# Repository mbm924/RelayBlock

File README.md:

# RelayBlock
A relay block pcb with current sensing for raspberry pi

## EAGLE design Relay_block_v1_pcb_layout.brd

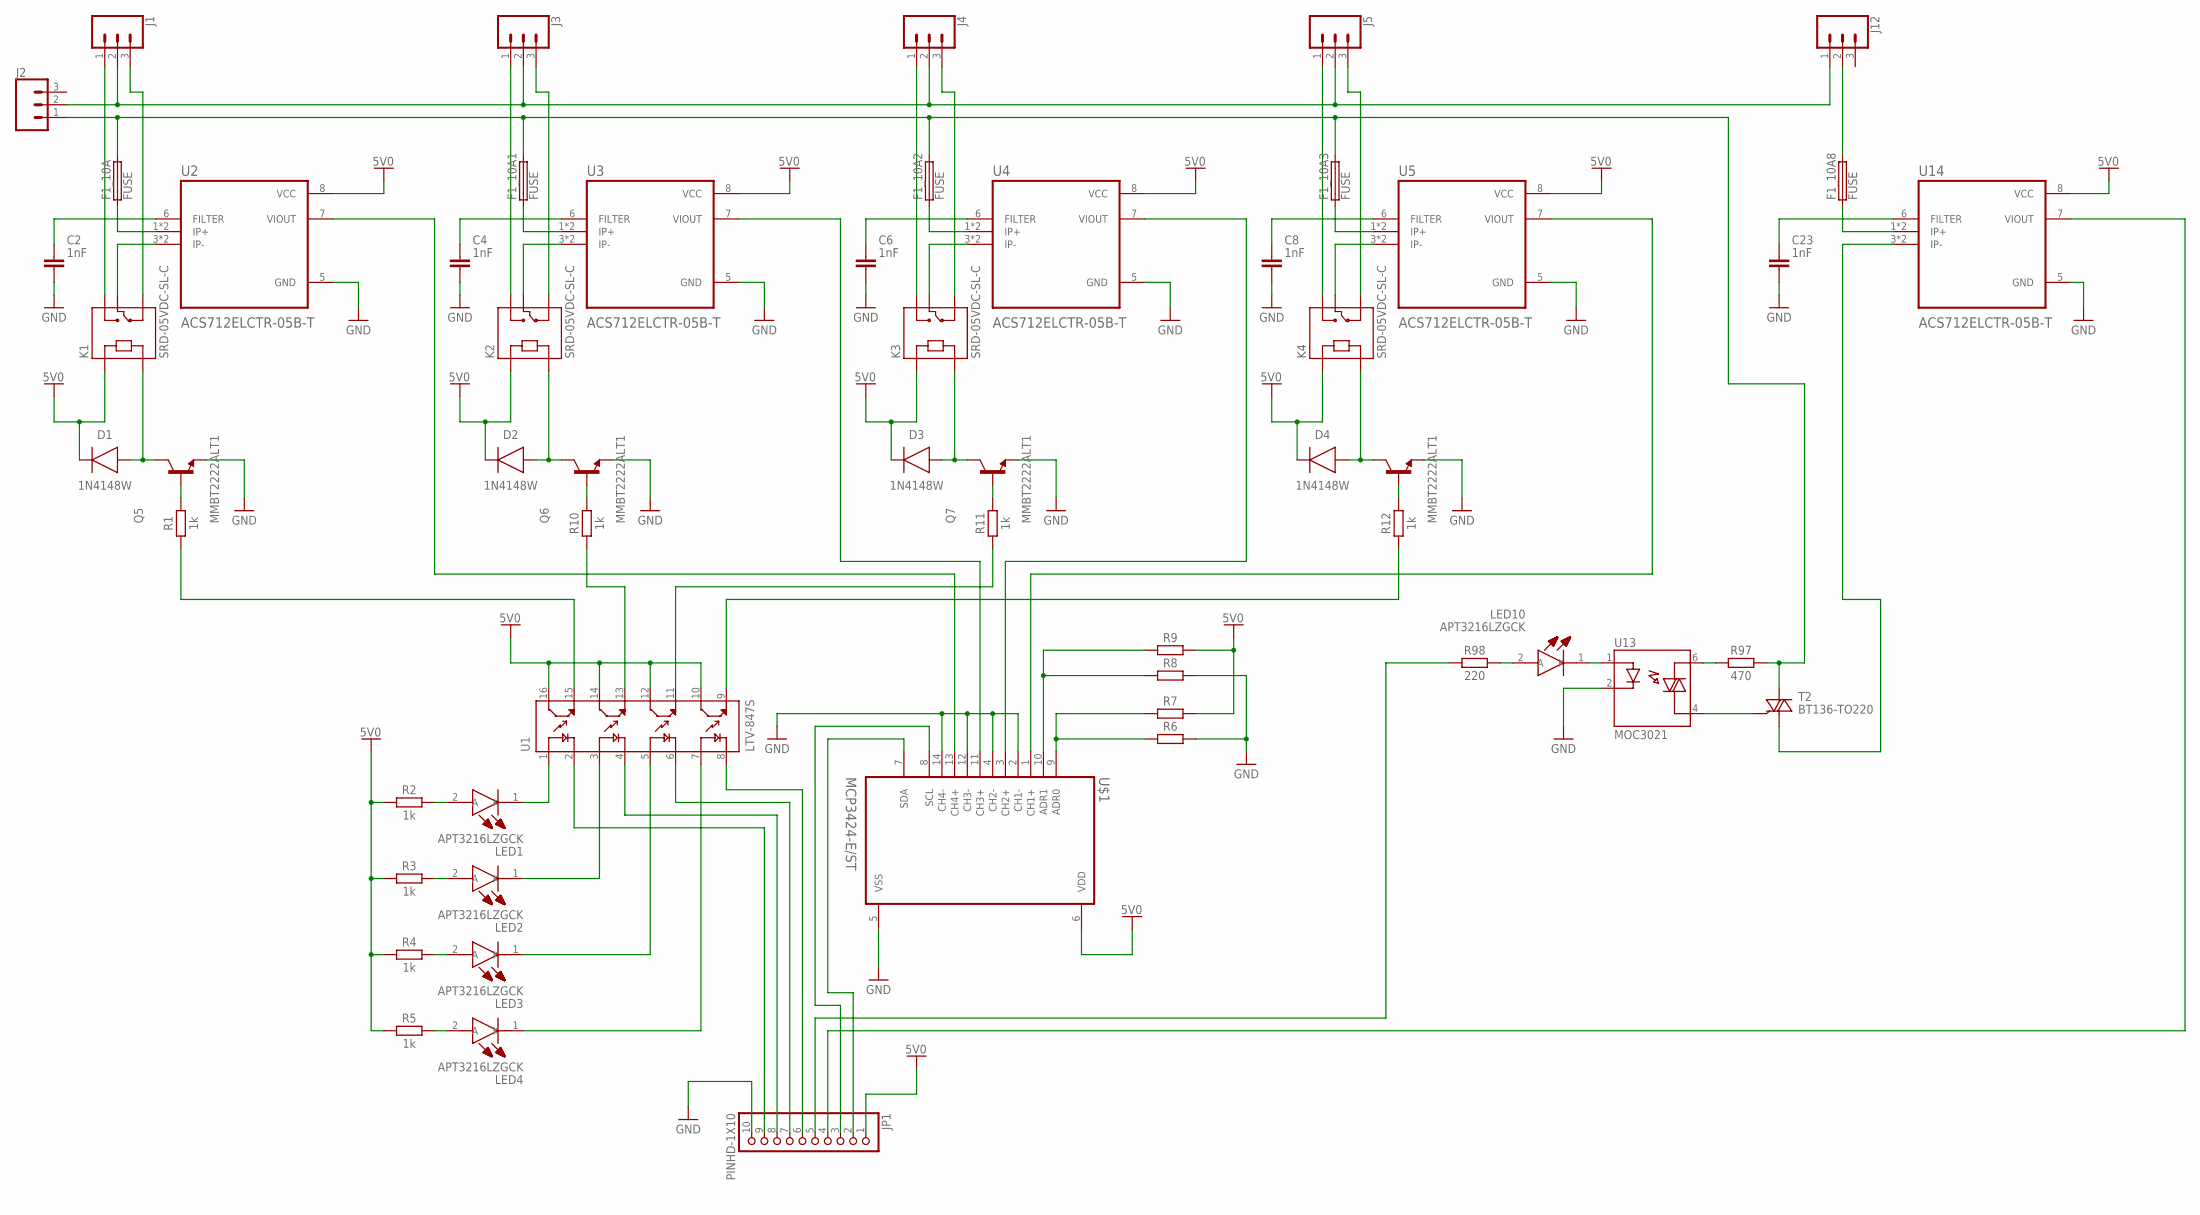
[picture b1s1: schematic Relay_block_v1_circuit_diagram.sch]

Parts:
C2, C4, C6, C8, C23: 1nF; CAPC3216X135
D1, D2, D3, D4: 1N4148W; SOD3715X135
F1_10A, F1_10A1, F1_10A2, F1_10A3, F1_10A8: FUSE; FUSC3215X82N
J1, J2, J3, J4, J5, J12: CONN_03-SCREW-5MM; SCREWTERMINAL-5MM-3
JP1: PINHD-1X10; 1X10
K1, K2, K3, K4: SRD-05VDC-SL-C; RELAY_SRD-05VDC-SL-C
LED1, LED2, LED3, LED4, LED10: APT3216LZGCK; LEDC3216X95N
Q5, Q6, Q7, Q8: MMBT2222ALT1; SOT95P237X111-3N
R1, R2, R3, R4, R5, R10, R11, R12: 1k; RESC3216X70
R6, R7, R8, R9: R_CHIP-1206(3216-METRIC); RESC3216X70
R97: 470; RESC3216X70
R98: 220; RESC3216X70
T2: BT136-TO220; TO220AB
U1: LTV-847S; SOIC254P1016X460-16N
U2, U3, U4, U5, U14: ACS712ELCTR-05B-T; SOIC127P600X175-8N
U13: MOC3021; DIP762W45P254L889H508Q6
U$1: MCP3424-E/ST; SOP65P640X120-14N

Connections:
5V0: D1.1 (C), D2.1 (C), D3.1 (C), D4.1 (C), JP1.1, K1.A1, K2.A1, K3.A1, K4.A1, R2.1, R3.1, R4.1, R5.1, R7.2, R9.2, U1.10 (CT3), U1.12 (CT2), U1.14 (CT1), U1.16 (CT), U2.8 (VCC), U3.8 (VCC), U4.8 (VCC), U5.8 (VCC), U14.8 (VCC), U$1.6 (VDD)
GND: C2.2, C4.2, C6.2, C8.2, C23.2, JP1.10, Q5.2 (E), Q6.2 (E), Q7.2 (E), Q8.2 (E), R6.2, R8.2, U2.5 (GND), U3.5 (GND), U4.5 (GND), U5.5 (GND), U13.2 (CATODE), U14.5 (GND), U$1.2 (CH1-), U$1.4 (CH2-), U$1.5 (VSS), U$1.12 (CH3-), U$1.14 (CH4-)
unnamed: LED2.2 (A), R3.2
unnamed: R1.1, U1.15 (ET)
unnamed: Q5.1 (B), R1.2
unnamed: K1.COM, U2.3 (IP-), U2.4 (IP-)
unnamed: LED1.2 (A), R2.2
unnamed: LED1.1 (K), U1.1 (A)
unnamed: LED2.1 (K), U1.3 (A1)
unnamed: LED3.2 (A), R4.2
unnamed: LED3.1 (K), U1.5 (A2)
unnamed: LED4.2 (A), R5.2
unnamed: LED4.1 (K), U1.7 (A3)
unnamed: D1.2 (A), K1.A2, Q5.3 (C)
unnamed: C2.1, U2.6 (FILTER)
unnamed: F1_10A.1, U2.1 (IP+), U2.2 (IP+)
unnamed: JP1.6, U1.8 (C3)
unnamed: J1.3, K1.NC
unnamed: J1.1, K1.NO
unnamed: JP1.7, U1.6 (C2)
unnamed: JP1.2, U$1.7 (SDA)
unnamed: J1.2, J2.2, J3.2, J4.2, J5.2, J12.1
unnamed: R8.1, R9.1, U$1.10 (ADR1)
unnamed: R6.1, R7.1, U$1.9 (ADR0)
unnamed: Q6.1 (B), R10.2
unnamed: D2.2 (A), K2.A2, Q6.3 (C)
unnamed: R10.1, U1.13 (ET1)
unnamed: K2.COM, U3.3 (IP-), U3.4 (IP-)
unnamed: C4.1, U3.6 (FILTER)
unnamed: F1_10A1.1, U3.1 (IP+), U3.2 (IP+)
unnamed: J3.3, K2.NC
unnamed: J3.1, K2.NO
unnamed: JP1.5, R98.1
unnamed: JP1.8, U1.4 (C1)
unnamed: Q7.1 (B), R11.2
unnamed: D3.2 (A), K3.A2, Q7.3 (C)
unnamed: R11.1, U1.11 (ET2)
unnamed: K3.COM, U4.3 (IP-), U4.4 (IP-)
unnamed: C6.1, U4.6 (FILTER)
unnamed: F1_10A2.1, U4.1 (IP+), U4.2 (IP+)
unnamed: J4.3, K3.NC
unnamed: J4.1, K3.NO
unnamed: JP1.9, U1.2 (C)
unnamed: JP1.4, U14.7 (VIOUT)
unnamed: Q8.1 (B), R12.2
unnamed: D4.2 (A), K4.A2, Q8.3 (C)
unnamed: R12.1, U1.9 (ET3)
unnamed: K4.COM, U5.3 (IP-), U5.4 (IP-)
unnamed: C8.1, U5.6 (FILTER)
unnamed: F1_10A3.1, U5.1 (IP+), U5.2 (IP+)
unnamed: J5.3, K4.NC
unnamed: J5.1, K4.NO
unnamed: U2.7 (VIOUT), U$1.13 (CH4+)
unnamed: U3.7 (VIOUT), U$1.11 (CH3+)
unnamed: U4.7 (VIOUT), U$1.3 (CH2+)
unnamed: U5.7 (VIOUT), U$1.1 (CH1+)
unnamed: F1_10A.2, F1_10A1.2, F1_10A2.2, F1_10A3.2, J2.1, R97.2, T2.2 (A2)
unnamed: F1_10A8.2, J12.2
unnamed: T2.1 (A1), U14.3 (IP-), U14.4 (IP-)
unnamed: T2.3 (G), U13.4 (MAIN_TERM2)
unnamed: LED10.2 (A), R98.2
unnamed: LED10.1 (K), U13.1 (ANODE)
unnamed: R97.1, U13.6 (MAIN_TERM1)
unnamed: JP1.3, U$1.8 (SCL)
unnamed: C23.1, U14.6 (FILTER)
unnamed: F1_10A8.1, U14.1 (IP+), U14.2 (IP+)

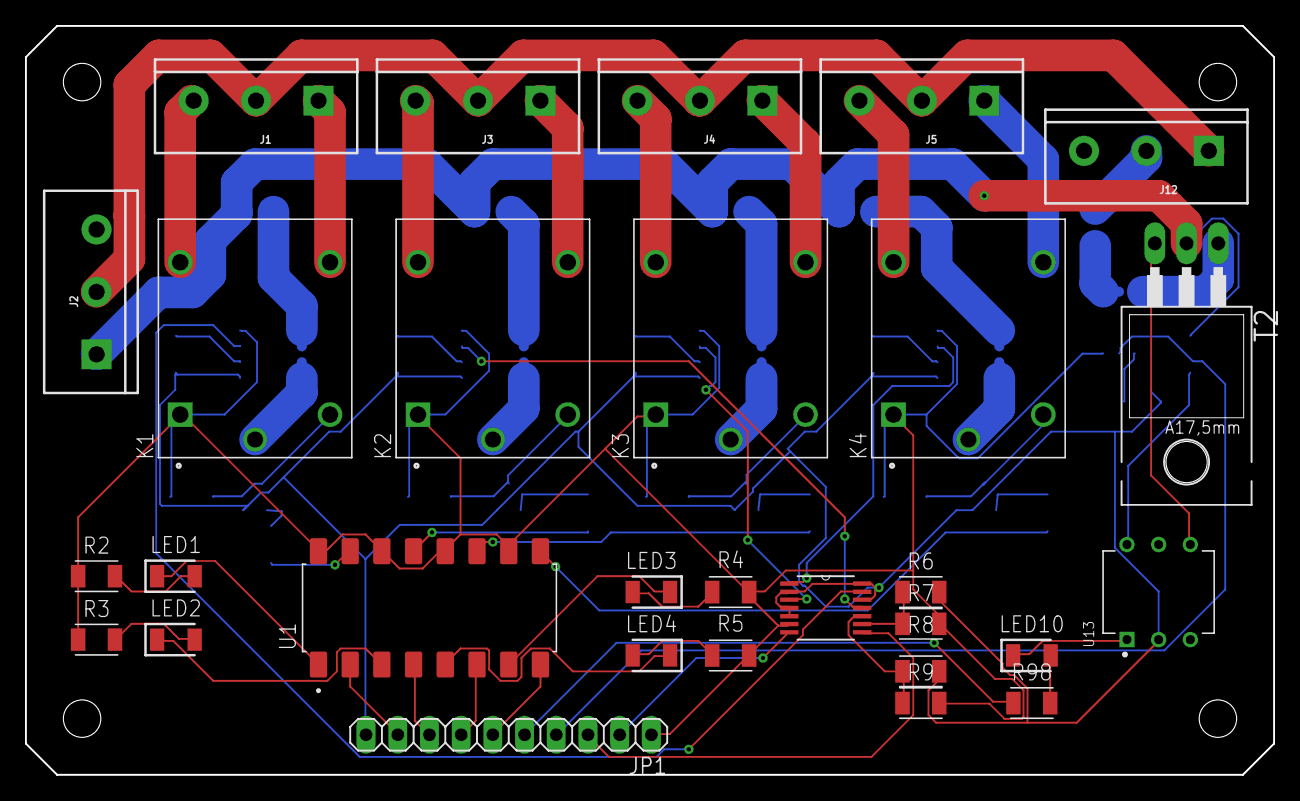
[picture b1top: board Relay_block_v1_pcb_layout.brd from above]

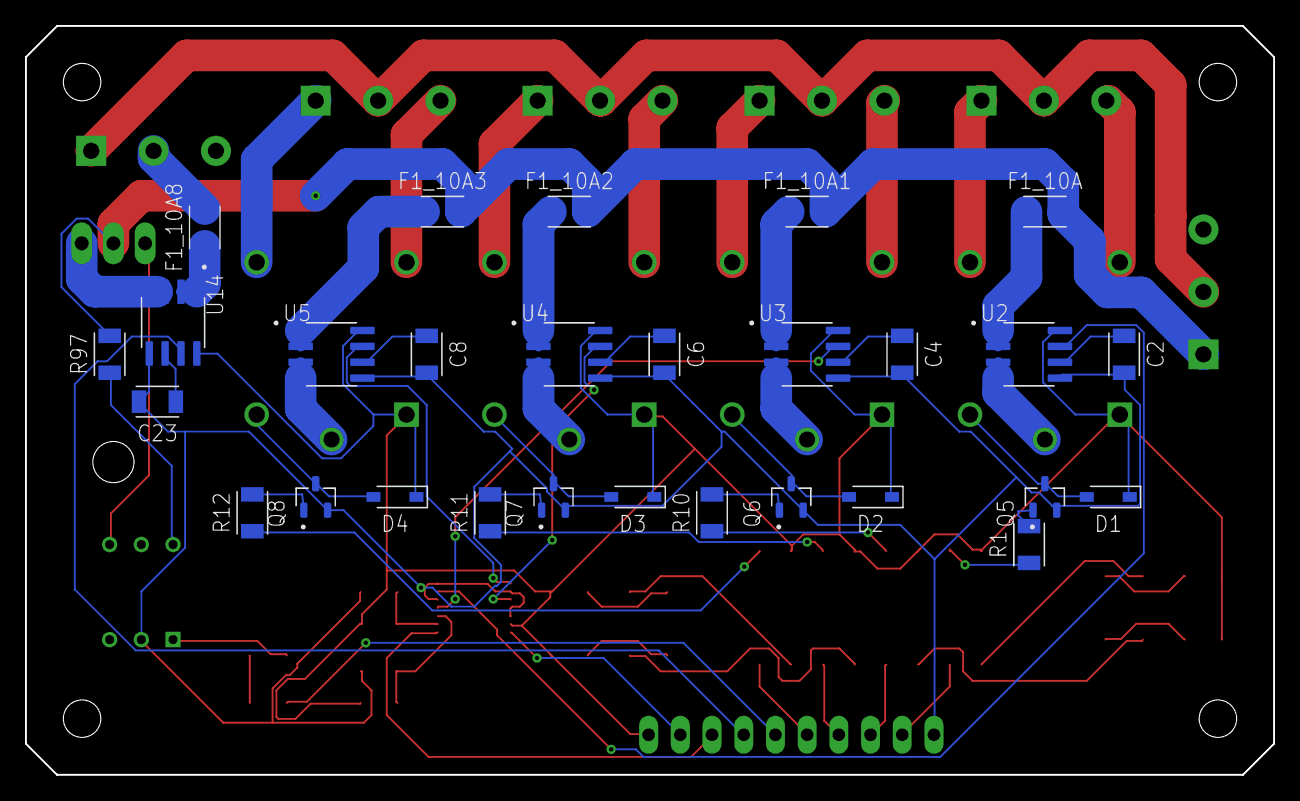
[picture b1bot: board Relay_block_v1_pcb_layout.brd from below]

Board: 2 copper layers, 100.0 x 60.0 mm, 57 parts (28 on the bottom side), 66 nets.

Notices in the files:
parts and their libraries:
SparkFun-Connectors: Licensing: Creative Commons ShareAlike 4.0 International - https://creativecommons.org/licenses/by-sa/4.0
